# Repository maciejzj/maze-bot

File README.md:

# MazeBot
Arduino/ATMega based mobile wheeled robot with DC motors controllers, created for a project at Silesian University of Technology.

The construction is actuated by DC motors. The robot avoids obstacles using an ultrasonic sensor mounted on top of a servo. The robot features a PI controller for synchronisation of the velocity of wheels and a cascade controller for precise turning. These control systems provide greater accuracy of movement, even with the most basic DC motors available.

The project consists of making a custom Arduino Leonardo clone PCB and designing a 3D printable chassis for the construction. Code is implemented using Arduino libraries and the bootloader.

The code and Autodesk Eagle files are stored in the GitHub repository, Autodesk Fusion 360 project files can be accessed using [Autodesk cloud mechanisms](https://a360.co/2U4947x).

Feel free to check out the documentation and [project report](https://raw.githubusercontent.com/MaciejZj/MazeBot/16cebf032a5ea0aaa41a32081933f3ef379c02ca/Documentation/POLSL_Project_Report_PL.pdf) in Polish.

The project uses modified [nonblocking ultrasonic Arduino library](https://github.com/jazzycamel/arduino).

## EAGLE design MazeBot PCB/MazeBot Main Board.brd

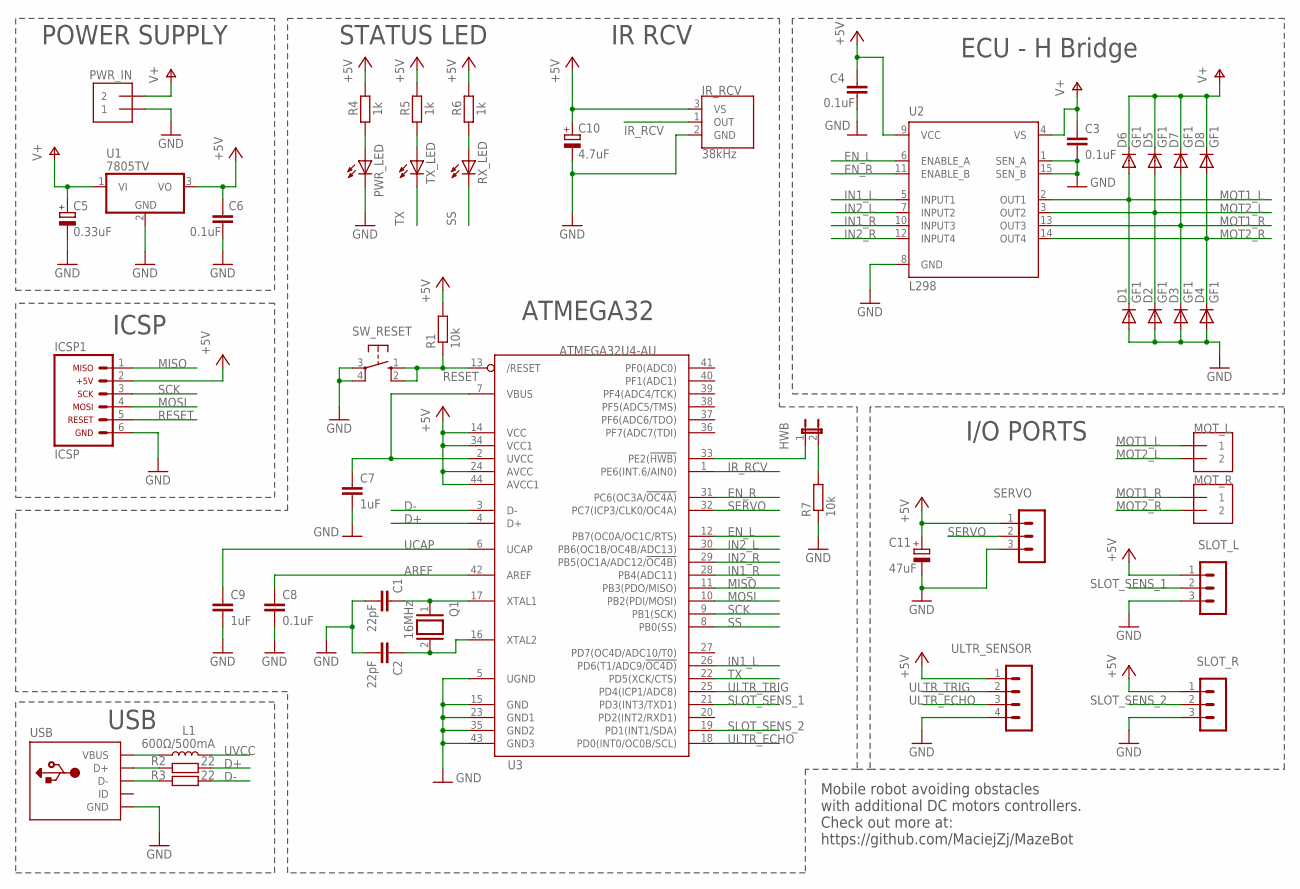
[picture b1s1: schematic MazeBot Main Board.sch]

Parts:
C1, C2: 22pF; C025-024X044
C3, C4, C6, C8: 0.1uF; C025-024X044
C5: 0.33uF; UD-4X5,8_NICHICON
C7, C9: 1uF; C025-024X044
C10: 4.7uF; UD-6,3X5,8_NICHICON
C11: 47uF; UD-6,3X5,8_NICHICON
D1, D2, D3, D4, D5, D6, D7, D8: GF1; SMA-DO214AC
HWB: JP1E; JP1
ICSP1: ARDUINO_CONN-ICSP; CONN-2X03
IR_RCV: 38kHz; TSOP382
L1: 600Ω/500mA; 0805
MOT_L: 1X2-3.5MM
MOT_R: 1X2-3.5MM
PWR_IN: 1X2-3.5MM
PWR_LED: LEDCHIP-LED0805; CHIP-LED0805
Q1: 16MHz; QS
R1, R7: 10k; R1206
R2, R3: 22; R1206
R4, R5, R6: 1k; R1206
RX_LED: LEDCHIP-LED0805; CHIP-LED0805
SERVO: MA03-1
SLOT_L: MA03-1
SLOT_R: MA03-1
SW_RESET: 10-XX; B3F-10XX
TX_LED: LEDCHIP-LED0805; CHIP-LED0805
U1: 7805TV; TO220V
U2: L298; MULTIWATT-15
U3: ATMEGA32U4-AU; TQFP44
ULTR_SENSOR: MA04-1
USB: USBMINIB; USB-MINIB

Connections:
+5V: C4.1, C6.1, C10.+, C11.+, ICSP1.2, IR_RCV.3 (VS), R1.2, R4.2, R5.2, R6.2, SERVO.1, SLOT_L.1, SLOT_R.1, U1.3 (VO), U2.9 (VCC), U3.14 (VCC), U3.24 (AVCC), U3.34 (VCC1), U3.44 (AVCC1), ULTR_SENSOR.1
AREF: C8.1, U3.42 (AREF)
D+: R2.1, U3.4 (D+)
D-: R3.1, U3.3 (D-)
EN_L: U2.6 (ENABLE_A), U3.12 (PB7(OC0A/OC1C/RTS))
EN_R: U2.11 (ENABLE_B), U3.31 (PC6(OC3A/!OC4A))
GND: C1.1, C2.2, C3.2, C4.2, C5.-, C6.2, C7.2, C8.2, C9.2, C10.-, C11.-, D1.A, D2.A, D3.A, D4.A, ICSP1.6, IR_RCV.2 (GND), PWR_IN.1, PWR_LED.C, R7.1, SERVO.3, SLOT_L.3, SLOT_R.3, SW_RESET.3, SW_RESET.4 (P1), U1.2 (GND), U2.1 (SEN_A), U2.8 (GND), U2.15 (SEN_B), U3.5 (UGND), U3.15 (GND), U3.23 (GND1), U3.35 (GND2), U3.43 (GND3), ULTR_SENSOR.4, USB.GND
IN1_L: U2.5 (INPUT1), U3.26 (PD6(T1/ADC9/!OC4D))
IN1_R: U2.10 (INPUT3), U3.28 (PB4(ADC11))
IN2_L: U2.7 (INPUT2), U3.30 (PB6(OC1B/OC4B/ADC13))
IN2_R: U2.12 (INPUT4), U3.29 (PB5(OC1A/ADC12/!OC4B))
IR_RCV: IR_RCV.1 (OUT), U3.1 (PE6(INT.6/AIN0))
MISO: ICSP1.1, U3.11 (PB3(PDO/MISO))
MOSI: ICSP1.4, U3.10 (PB2(PDI/MOSI))
MOT1_L: D1.K (C), D6.A, MOT_L.1, U2.2 (OUT1)
MOT1_R: D3.K (C), D7.A, MOT_R.1, U2.13 (OUT3)
MOT2_L: D2.K (C), D5.A, MOT_L.2, U2.3 (OUT2)
MOT2_R: D4.K (C), D8.A, MOT_R.2, U2.14 (OUT4)
unnamed: C1.2, Q1.1, U3.17 (XTAL1)
unnamed: C2.1, Q1.2, U3.16 (XTAL2)
unnamed: PWR_LED.A, R4.1
unnamed: R2.2, USB.D+
unnamed: R3.2, USB.D-
unnamed: R5.1, TX_LED.A
unnamed: R6.1, RX_LED.A
unnamed: HWB.1, U3.33 (PE2(!HWB))
unnamed: HWB.2, R7.2
unnamed: L1.1, USB.VBUS
RESET: ICSP1.5, R1.1, SW_RESET.1 (S), SW_RESET.2 (S1), U3.13 (/RESET)
SCK: ICSP1.3, U3.9 (PB1(SCK))
SERVO: SERVO.2, U3.32 (PC7(ICP3/CLK0/OC4A))
SLOT_SENS_1: SLOT_L.2, U3.21 (PD3(INT3/TXD1))
SLOT_SENS_2: SLOT_R.2, U3.19 (PD1(INT1/SDA))
SS: RX_LED.C, U3.8 (PB0(SS))
TX: TX_LED.C, U3.22 (PD5(XCK/CTS))
UCAP: C9.1, U3.6 (UCAP)
ULTR_ECHO: U3.18 (PD0(INT0/OC0B/SCL)), ULTR_SENSOR.3
ULTR_TRIG: U3.25 (PD4(ICP1/ADC8)), ULTR_SENSOR.2
UVCC: C7.1, L1.2, U3.2 (UVCC), U3.7 (VBUS)
V+: C3.1, C5.+, D5.K (C), D6.K (C), D7.K (C), D8.K (C), PWR_IN.2, U1.1 (VI), U2.4 (VS)

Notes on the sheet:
POWER SUPPLY
ECU - H Bridge
ICSP
USB
STATUS LED
ATMEGA32
IR RCV
I/O PORTS
Mobile robot avoiding obstacles with additional DC motors controllers. Check out more at: https://github.com/MaciejZj/MazeBot

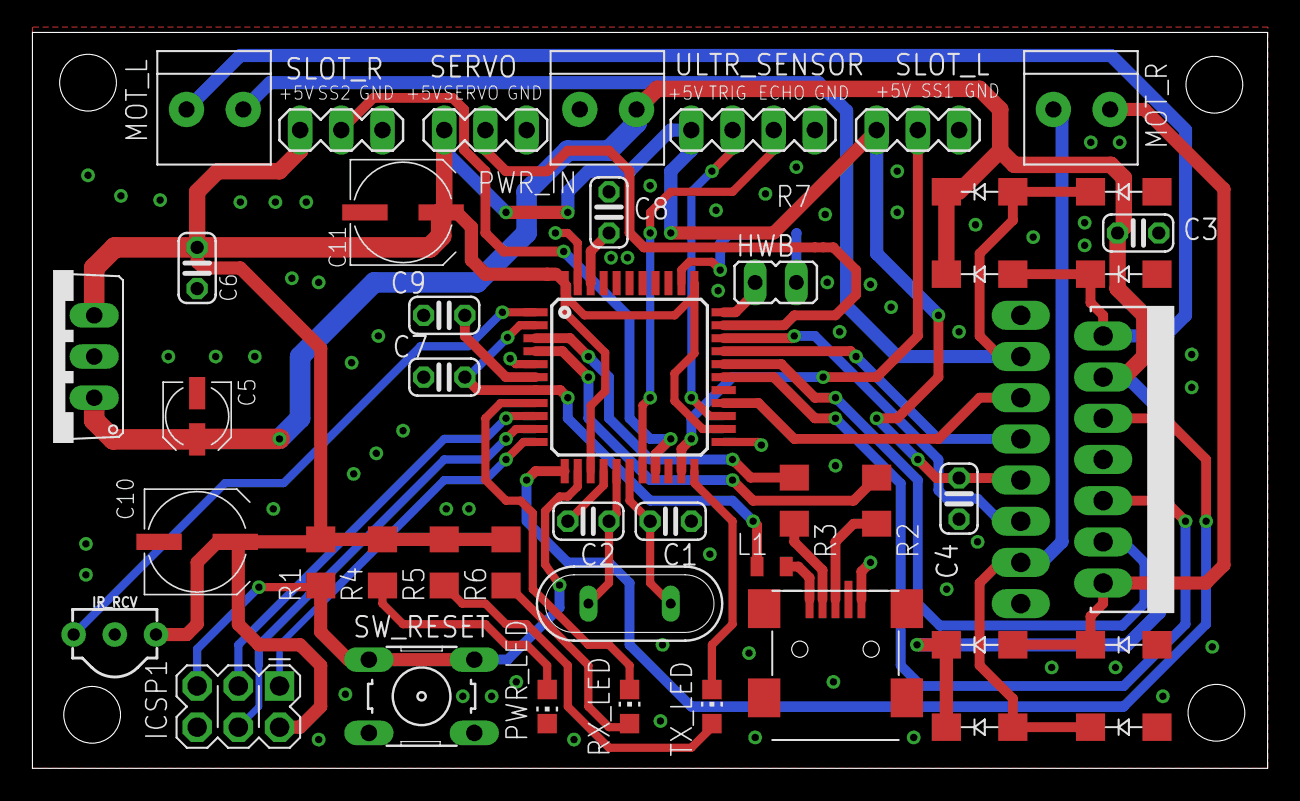
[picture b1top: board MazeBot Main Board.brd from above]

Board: 2 copper layers, 76.2 x 45.4 mm, 46 parts (1 on the bottom side), 40 nets.

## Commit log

2018-10-27 Update gitignore
2018-10-27 Add motor directions defines
2018-10-27 Create platformMotors declarations
2018-10-27 Create servoSensor declarations
2018-10-27 Configure motors GPIO pinout
2018-10-27 Create servoSensor turning function
2018-10-27 Configure servo GPIO pinout
2018-10-27 Fill motors steering functions
2018-10-27 Import HC_SR04 ultrasonic sensor library
2018-10-27 Setup ultrasonic sensor
2018-10-27 Stop if obstacle is detected
2018-10-27 Add blocking ultrasonic sensor probing function
2018-10-27 Fix motor functions arguments
2018-10-27 Select turning direction as func argument
2018-10-27 Fix default arguments in motor functions
2018-10-27 Search for direction with no obstacles
2018-10-29 Move searching for an unobstructed path to func
2018-10-29 Use finding direction func in main loop
2018-10-30 Fix bugs detected when testing with hardware
2018-10-30 Add delay after motor stop
2018-10-30 Measure time of moving forward
2018-11-01 Add func to move half of the len of the platform
2018-11-01 Create corridorEscaper func
2018-11-02 Setup IR receiver
2018-11-02 Create func for IR interrupt
2018-11-02 Make defines for program states
2018-11-02 Move main loop to state machine
2018-11-02 Disable corridorEscaper till fix
2018-11-11 New pinout and variables for PoC and slot sensors
    Resolves: #18
2018-11-11 Slot sensors setup and counter interrupts
2018-11-12 Split left and right motors stopping
2018-11-12 Add macros for slot numbers calculation
2018-11-12 Macros fix
2018-11-22 Add time delta vars and calculation
2018-11-22 Add separate motor velocity and direction func
2018-11-27 Heading regulator prototype
2018-11-27 Fix defines typo
2018-11-28 Create Eagle PCB project
2018-11-28 Add stabiliser schematic
2018-11-28 Add ECU schematic
2018-11-28 Add ATMEGA with XTAL
2018-11-28 Add power for ATMEGA
2018-11-28 Wire ICSP for ATMEGA
2018-11-29 Add USB schematic
2018-11-30 Add signal routes
2018-11-30 Move inside a frame
2018-11-30 Add status diodes
2018-11-30 Add IR remote
2018-11-30 Add IO Ports
2018-11-30 Fix major ERC issues
2018-11-30 Create PCB board file
2018-11-30 Fix minor shematic issues
2018-11-30 Add power in terminal
2018-12-05 Change to SMD and minor fixes
2018-12-06 Route PCB with SMD
2018-12-06 Add mounting screw holes
2018-12-10 Fix ground connections
2018-12-10 Fix DRC
2018-12-10 Fix libraries nums on pads
2018-12-10 Add goldpin descriptions
2018-12-10 Minor fixes
2018-12-10 Add HWB grounding
2018-12-11 Add jumper to HWB
2018-12-11 Fix XTAL caps
2019-01-02 Final PCB pinout and globals
2019-01-02 Cleanup some initialisation code
2019-01-02 Cleanup motor baisc utilities functions
2019-01-02 Turning regulator full draft
2019-01-02 Update direction turning utility
2019-01-02 Update slot sensors ISRs
2019-01-02 Enhance straight heding regulator
2019-01-02 Fix typos
2019-01-02 Remove old code not based on regulators
2019-01-02 Clear main to match new motors controls
2019-01-02 Fix more typos
2019-01-02 Upload fixes
    Repairs left encoder ISR, removes inlines and adds delay to turning.
2019-01-03 Add debug macros
2019-01-03 Add more documentation
2019-01-05 PCB print day upload
2019-01-05 Import identification files
2019-01-07 Create model identification function
2019-01-07 Analyse csv data and draw root locus
2019-01-07 Create report TOC
2019-01-07 Add abstract
2019-01-07 Add introduction and schedule
2019-01-07 Add prototyping description
2019-01-09 Add components specification
2019-01-09 Mv documentation to separate dir
2019-01-11 Update report PCB and chasis desc
2019-01-18 Add regulators documentation
2019-01-18 Finish documentation draft
2019-01-18 Move documentation TOC to new page
2019-01-18 Move listings to minted
2019-01-18 Final schamtic cleanup for documentation
2019-01-18 Schematic and PCB images and doc tweaks
2019-01-18 Update gitingore for LaTex again
2019-01-20 Add comments to identif script
2019-01-20 Update Eagle proj
2019-01-20 Import Matlab charts and platf drawing
2019-01-20 Create tikz control block charts
2019-01-20 Create tikz flowchart
2019-01-20 Update report to gathered materials
2019-01-20 Fix doc typos
2019-01-20 Update doc biblio
2019-01-20 Fix transfer func typo in doc
2019-01-21 Make better abstract description
2019-01-21 Further fix and rerender abstract
2019-01-26 Cleanup tex files
2019-01-26 Spaces for comments alignement
2019-01-26 Fix indentation
2019-01-26 Fix indentation again
2019-01-26 Fix indentation once more
2019-01-26 Further cleanup
2019-01-26 More cleanup
2019-01-26 Cleanup after merge
2019-01-26 Fix documentation listings
2019-01-27 Eagle major upgrade
2019-02-02 Add documentation videos
2019-02-02 Add img to readme
2019-02-02 Fix units in doc and finally indentation
2019-02-02 Fix grammar in doc
2019-04-25 Add forgotten acknowledgments
2019-04-25 Create LICENSE
2019-07-28 Rework title page with more images
2019-07-28 Go back to original date of release
2019-08-26 More images in docs
2019-08-26 Add more images to README
2019-08-26 Compress images
2020-04-10 Add gifs
2020-05-04 Rm windows endlines

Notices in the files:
parts and their libraries:
SparkFun-Sensors: Licensing: Creative Commons ShareAlike 4.0 International - https://creativecommons.org/licenses/by-sa/4.0
